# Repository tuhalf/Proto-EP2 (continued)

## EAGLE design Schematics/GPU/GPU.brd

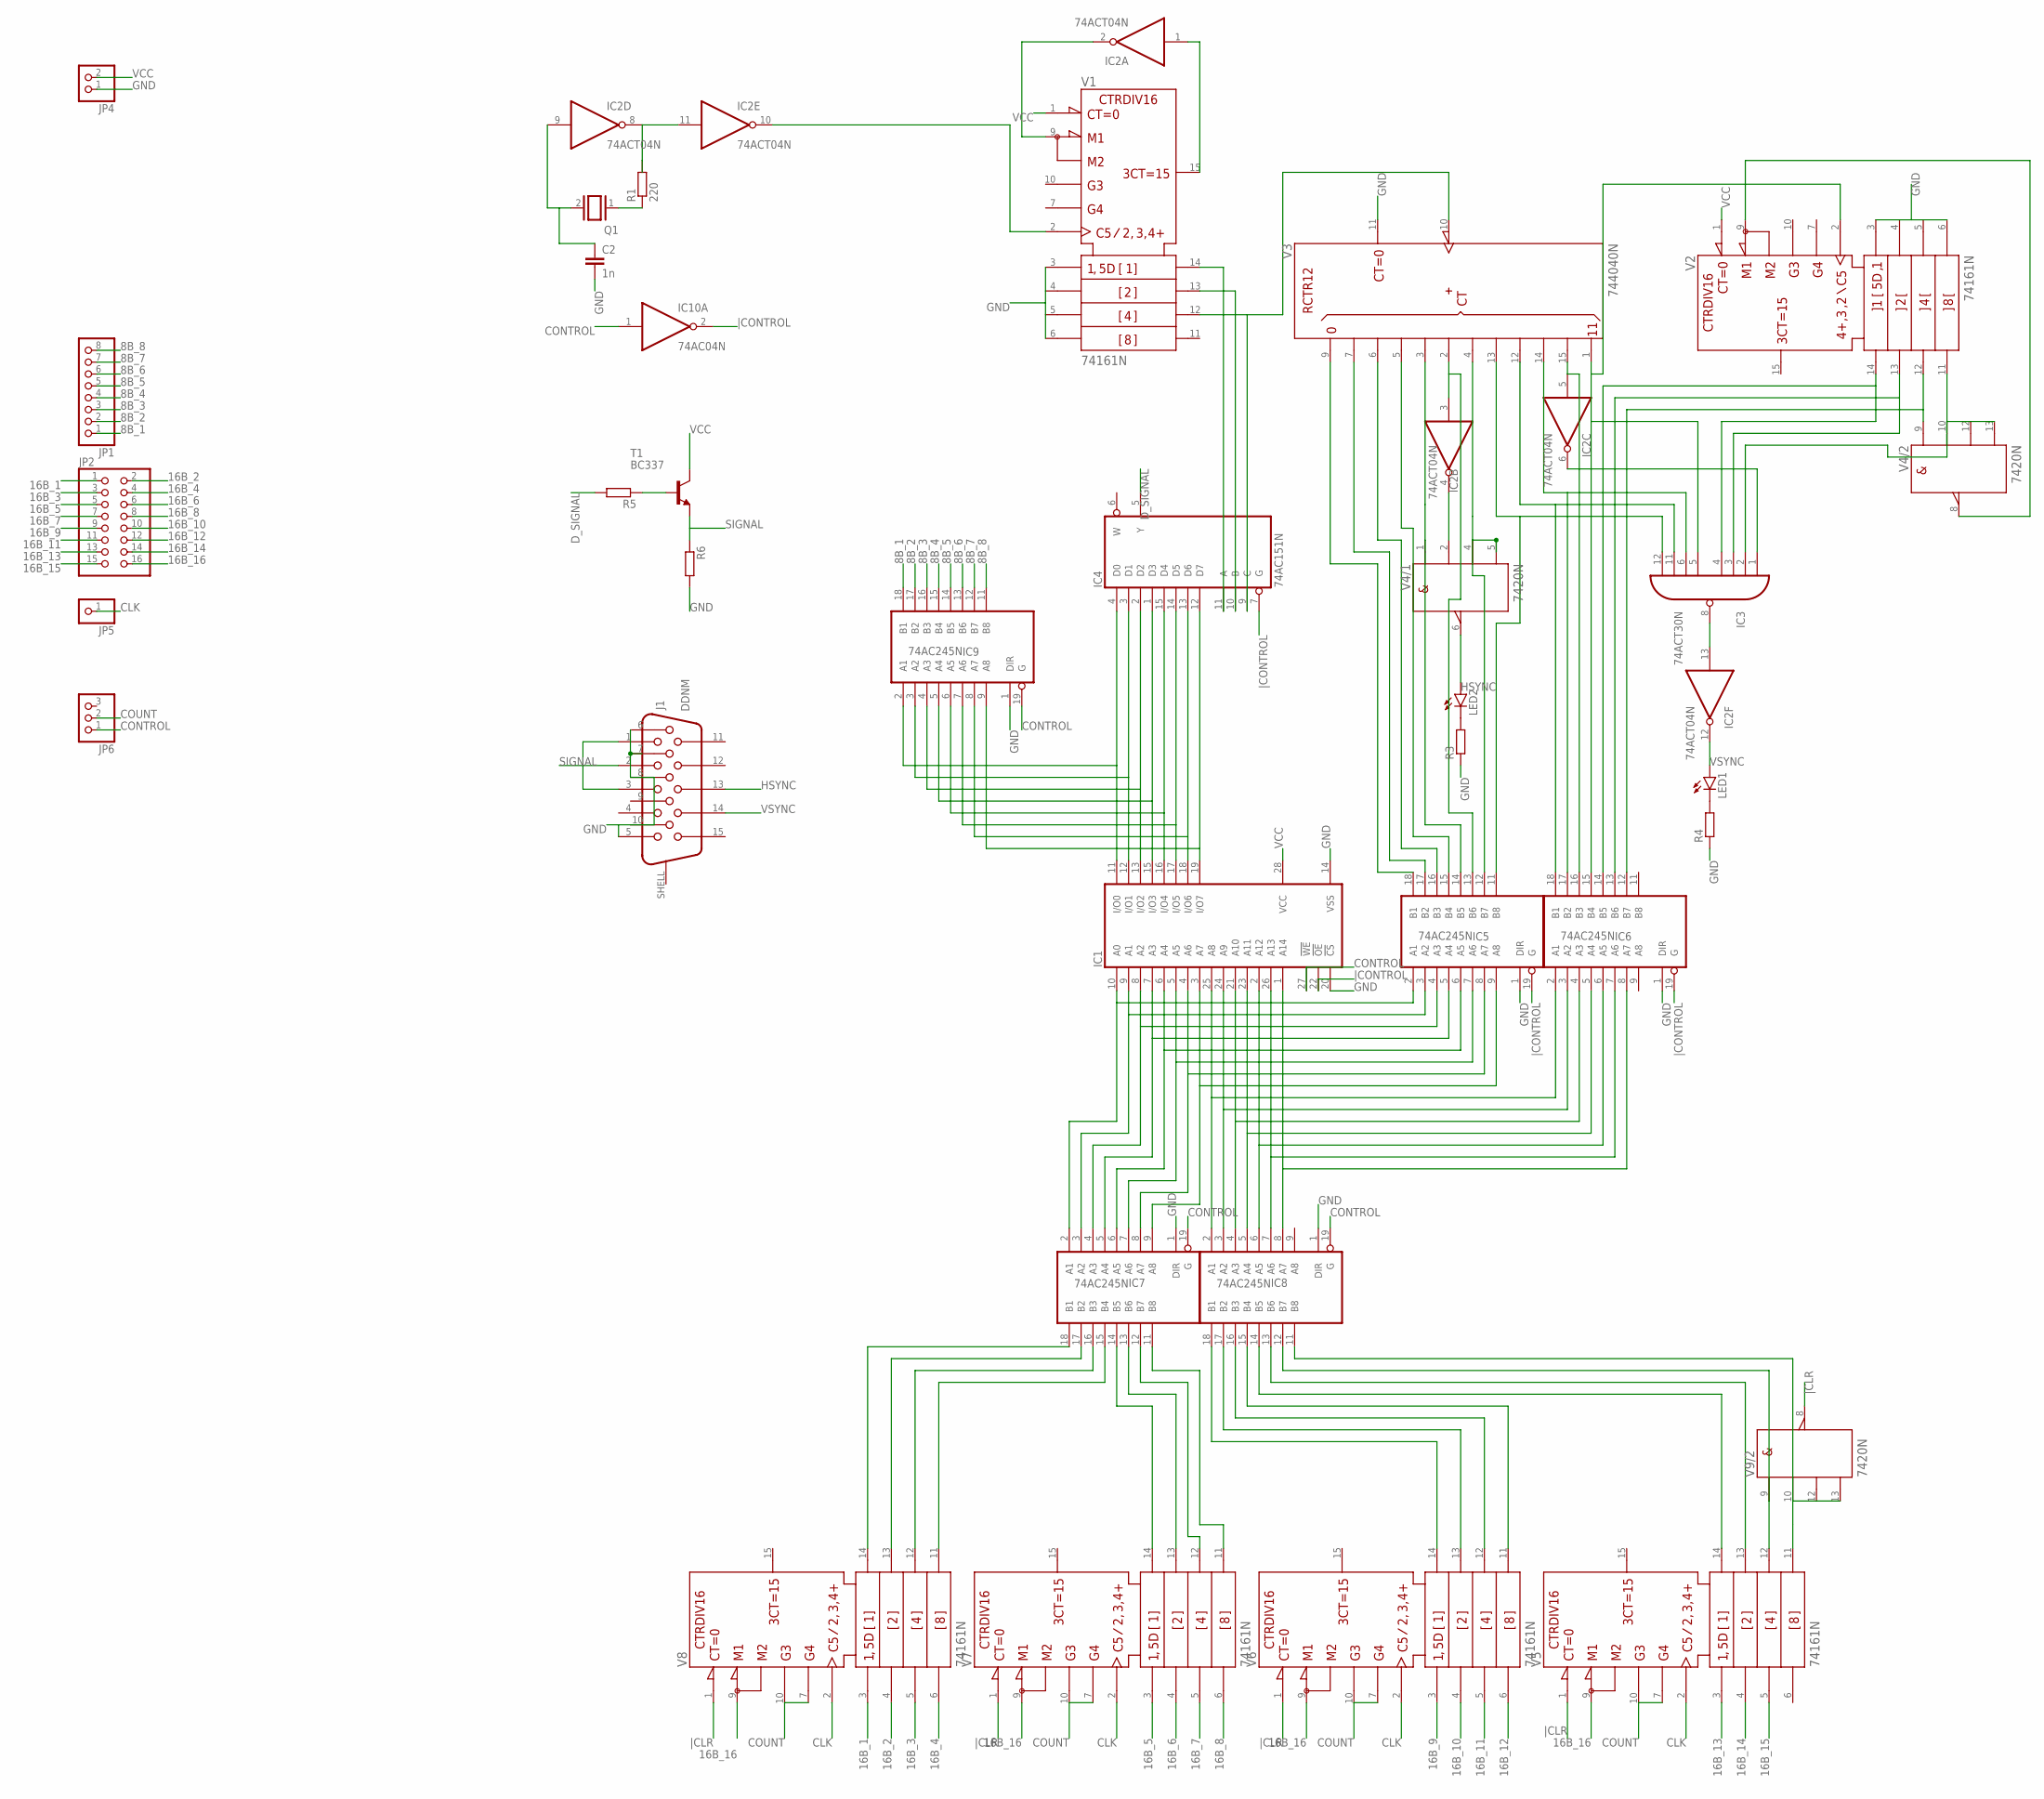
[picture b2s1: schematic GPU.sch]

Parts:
C2: 1n; C025-025X050
IC1: 62256P; DIL28-6
IC2: 74ACT04N; DIL14
IC3: 74ACT30N; DIL14
IC4: 74AC151N; DIL16
IC5, IC6, IC7, IC8, IC9: 74AC245N; DIL20
IC10: 74AC04N; DIL14
J1: DDNM; DNM
JP1: PINHD-1X8; 1X08
JP2: PINHD-2X8; 2X08
JP4: PINHD-1X2; 1X02
JP5: PINHD-1X1; 1X01
JP6: PINHD-1X3; 1X03
LED1, LED2: LED5MM
Q1: XTAL/S; QS
R1: 220; 0204/7
R3, R4, R5, R6: R-EU_0204/7; 0204/7
T1: BC337; TO92
V1, V2, V5, V6, V7, V8: 74161N; DIL16
V3: 744040N; DIL16
V4, V9: 7420N; DIL14

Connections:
8B_1: IC9.18 (B1), JP1.1
8B_2: IC9.17 (B2), JP1.2
8B_3: IC9.16 (B3), JP1.3
8B_4: IC9.15 (B4), JP1.4
8B_5: IC9.14 (B5), JP1.5
8B_6: IC9.13 (B6), JP1.6
8B_7: IC9.12 (B7), JP1.7
8B_8: IC9.11 (B8), JP1.8
16B_1: JP2.1, V8.3 (A)
16B_2: JP2.2, V8.4 (B)
16B_3: JP2.3, V8.5 (C)
16B_4: JP2.4, V8.6 (D)
16B_5: JP2.5, V7.3 (A)
16B_6: JP2.6, V7.4 (B)
16B_7: JP2.7, V7.5 (C)
16B_8: JP2.8, V7.6 (D)
16B_9: JP2.9, V6.3 (A)
16B_10: JP2.10, V6.4 (B)
16B_11: JP2.11, V6.5 (C)
16B_12: JP2.12, V6.6 (D)
16B_13: JP2.13, V5.3 (A)
16B_14: JP2.14, V5.4 (B)
16B_15: JP2.15, V5.5 (C)
16B_16: JP2.16, V5.9 (!LOAD), V6.9 (!LOAD), V7.9 (!LOAD), V8.9 (!LOAD)
+UB: V1.16 (+UB), V2.16 (+UB), V3.16 (+UB), V4.14 (+UB), V5.16 (+UB), V6.16 (+UB), V7.16 (+UB), V8.16 (+UB), V9.14 (+UB)
-UB: V1.8 (-UB), V2.8 (-UB), V3.8 (-UB), V4.7 (-UB), V5.8 (-UB), V6.8 (-UB), V7.8 (-UB), V8.8 (-UB), V9.7 (-UB)
CLK: JP5.1, V5.2 (CLK), V6.2 (CLK), V7.2 (CLK), V8.2 (CLK)
CONTROL: IC1.27 (!WE), IC7.19 (G), IC8.19 (G), IC9.19 (G), IC10.1 (I), JP6.1
COUNT: JP6.2, V5.7 (ENP), V5.10 (ENT), V6.7 (ENP), V6.10 (ENT), V7.7 (ENP), V7.10 (ENT), V8.7 (ENP), V8.10 (ENT)
D_SIGNAL: IC4.5 (Y), R5.2
GND: C2.2, IC1.14 (VSS), IC1.20 (!CS), IC2.7 (GND), IC3.7 (GND), IC4.8 (GND), IC5.1 (DIR), IC5.10 (GND), IC6.1 (DIR), IC6.10 (GND), IC7.1 (DIR), IC7.10 (GND), IC8.1 (DIR), IC8.10 (GND), IC9.1 (DIR), IC9.10 (GND), IC10.7 (GND), J1.5, J1.6, J1.7, J1.8, J1.10, JP4.1, R3.1, R4.1, R6.2, V1.3 (A), V1.4 (B), V1.5 (C), V1.6 (D), V2.3 (A), V2.4 (B), V2.5 (C), V2.6 (D), V3.11 (CLR)
HSYNC: J1.13, LED2.A, V4.6 (Y)
unnamed: C2.1, IC2.9 (I), Q1.2
unnamed: Q1.1, R1.1
unnamed: IC2.10 (O), V1.2 (CLK)
unnamed: IC2.2 (O), V1.9 (!LOAD)
unnamed: IC4.9 (C), V1.12 (QC), V3.10 (CLK)
unnamed: IC2.1 (I), V1.15 (RCO)
unnamed: IC5.18 (B1), V3.9 (QA)
unnamed: IC5.17 (B2), V3.7 (QB)
unnamed: IC5.14 (B5), V3.3 (QE), V4.1 (A)
unnamed: IC5.12 (B7), V3.4 (QG), V4.4 (C), V4.5 (D)
unnamed: IC3.5 (I4), IC6.15 (B4), V2.2 (CLK), V3.1 (QL)
unnamed: IC3.12 (I7), IC5.11 (B8), V3.13 (QH)
unnamed: V2.9 (!LOAD), V4.8 (Y)
unnamed: IC1.10 (A0), IC5.2 (A1), IC7.2 (A1)
unnamed: IC3.2 (I1), V2.11 (QD), V4.10 (B), V4.12 (C), V4.13 (D)
unnamed: IC3.11 (I6), IC6.18 (B1), V3.12 (QI)
unnamed: IC3.6 (I5), IC6.17 (B2), V3.14 (QJ)
unnamed: IC3.4 (I3), IC6.14 (B5), V2.14 (QA)
unnamed: IC3.3 (I2), IC6.13 (B6), V2.13 (QB)
unnamed: IC2.5 (I), IC6.16 (B3), V3.15 (QK)
unnamed: IC2.6 (O), IC3.1 (I0)
unnamed: IC2.13 (I), IC3.8 (O)
unnamed: IC4.11 (A), V1.14 (QA)
unnamed: IC4.10 (B), V1.13 (QB)
unnamed: IC5.16 (B3), V3.6 (QC)
unnamed: R5.1, T1.2 (B)
unnamed: LED2.K (C), R3.2
unnamed: LED1.K (C), R4.2
unnamed: IC2.8 (O), IC2.11 (I), R1.2
unnamed: IC5.15 (B4), V3.5 (QD)
unnamed: IC1.9 (A1), IC5.3 (A2), IC7.3 (A2)
unnamed: IC1.8 (A2), IC5.4 (A3), IC7.4 (A3)
unnamed: IC1.7 (A3), IC5.5 (A4), IC7.5 (A4)
unnamed: IC2.4 (O), V4.2 (B)
unnamed: IC1.6 (A4), IC5.6 (A5), IC7.6 (A5)
unnamed: IC6.12 (B7), V2.12 (QC), V4.9 (A)
unnamed: IC1.5 (A5), IC5.7 (A6), IC7.7 (A6)
unnamed: IC1.4 (A6), IC5.8 (A7), IC7.8 (A7)
unnamed: IC2.3 (I), IC5.13 (B6), V3.2 (QF)
unnamed: IC1.3 (A7), IC5.9 (A8), IC7.9 (A8)
unnamed: IC1.25 (A8), IC6.2 (A1), IC8.2 (A1)
unnamed: IC1.24 (A9), IC6.3 (A2), IC8.3 (A2)
unnamed: IC1.21 (A10), IC6.4 (A3), IC8.4 (A3)
unnamed: IC1.23 (A11), IC6.5 (A4), IC8.5 (A4)
unnamed: IC1.2 (A12), IC6.6 (A5), IC8.6 (A5)
unnamed: IC1.26 (A13), IC6.7 (A6), IC8.7 (A6)
unnamed: IC1.1 (A14), IC6.8 (A7), IC8.8 (A7)
unnamed: IC8.12 (B7), V5.12 (QC), V9.9 (A)
unnamed: IC8.11 (B8), V5.11 (QD), V9.10 (B), V9.12 (C), V9.13 (D)
unnamed: IC7.18 (B1), V8.14 (QA)
unnamed: IC7.17 (B2), V8.13 (QB)
unnamed: IC7.16 (B3), V8.12 (QC)
unnamed: IC7.15 (B4), V8.11 (QD)
unnamed: IC7.14 (B5), V7.14 (QA)
unnamed: IC7.13 (B6), V7.13 (QB)
unnamed: IC7.12 (B7), V7.12 (QC)
unnamed: IC7.11 (B8), V7.11 (QD)
unnamed: IC8.18 (B1), V6.14 (QA)
unnamed: IC8.13 (B6), V5.13 (QB)
unnamed: IC8.14 (B5), V5.14 (QA)
unnamed: IC8.15 (B4), V6.11 (QD)
unnamed: IC8.16 (B3), V6.12 (QC)
unnamed: IC8.17 (B2), V6.13 (QB)
unnamed: IC1.19 (I/O7), IC4.12 (D7), IC9.9 (A8)
unnamed: IC1.17 (I/O5), IC4.14 (D5), IC9.7 (A6)
unnamed: IC1.18 (I/O6), IC4.13 (D6), IC9.8 (A7)
unnamed: IC1.16 (I/O4), IC4.15 (D4), IC9.6 (A5)
unnamed: IC1.15 (I/O3), IC4.1 (D3), IC9.5 (A4)
unnamed: IC1.13 (I/O2), IC4.2 (D2), IC9.4 (A3)
unnamed: IC1.12 (I/O1), IC4.3 (D1), IC9.3 (A2)
unnamed: IC1.11 (I/O0), IC4.4 (D0), IC9.2 (A1)
SIGNAL: J1.1, J1.2, J1.3, R6.1, T1.1 (E)
VCC: IC1.28 (VCC), IC2.14 (VCC), IC3.14 (VCC), IC4.16 (VCC), IC5.20 (VCC), IC6.20 (VCC), IC7.20 (VCC), IC8.20 (VCC), IC9.20 (VCC), IC10.14 (VCC), JP4.2, T1.3 (C), V1.1 (!CLR), V2.1 (!CLR)
VSYNC: IC2.12 (O), J1.14, LED1.A
|CLR: V5.1 (!CLR), V6.1 (!CLR), V7.1 (!CLR), V8.1 (!CLR), V9.8 (Y)
|CONTROL: IC1.22 (!OE), IC4.7 (G), IC5.19 (G), IC6.19 (G), IC10.2 (O)

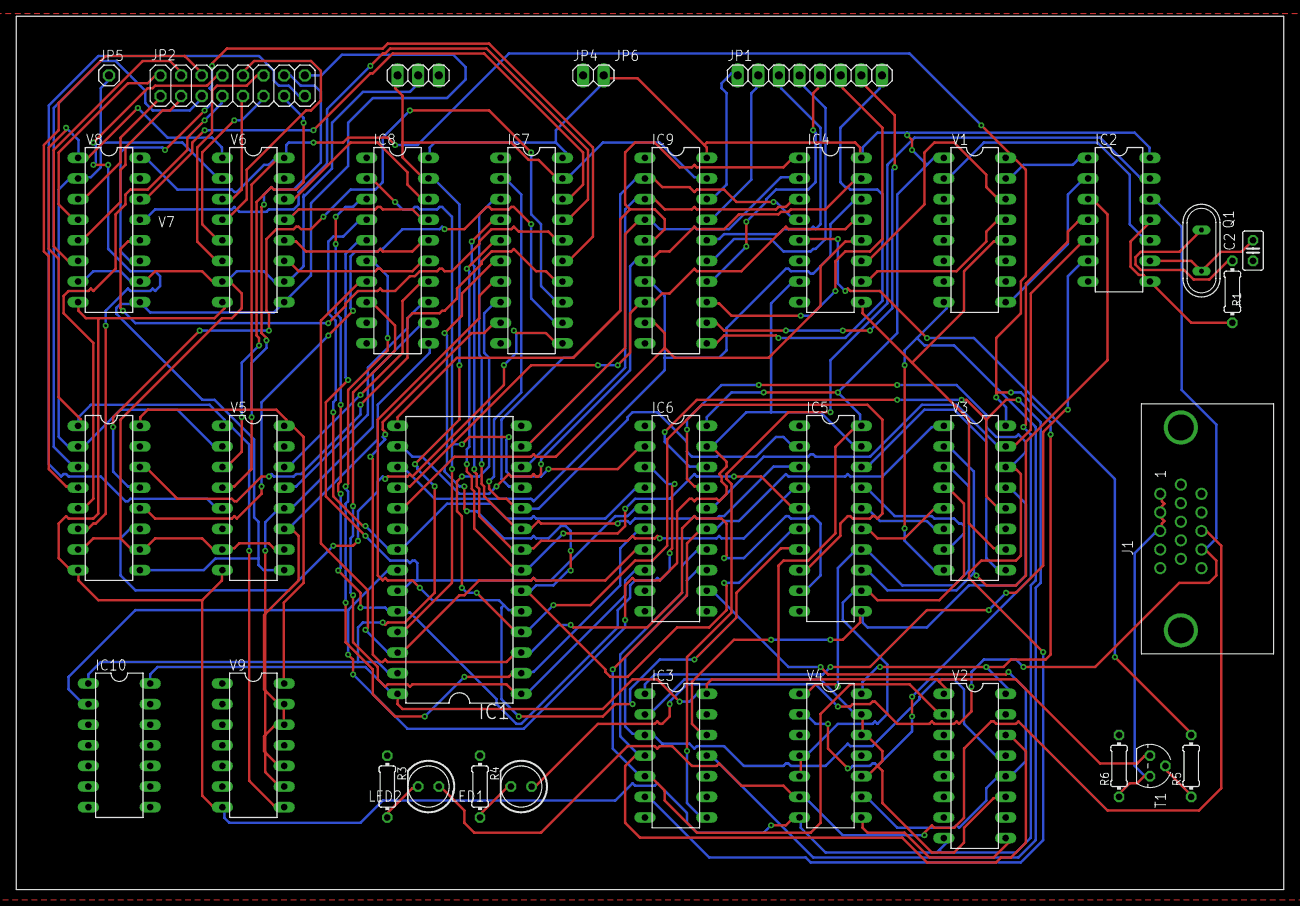
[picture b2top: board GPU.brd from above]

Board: 2 copper layers, 156.2 x 107.6 mm, 35 parts (0 on the bottom side), 108 nets.

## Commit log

2019-04-26 Simulation Created
2019-04-26 Perfected
2019-04-27 Bug Fix
2019-04-27 Started Eagle Drawings
2019-04-28 Some Modules Added
    Ram, Pc, A and B registers and ALU added.
2019-04-30 Schematics Are Done
2019-04-30 Some Changes
2019-05-01 made README better
2019-05-01 made README even better
2019-05-01 Added instruction set documentation
2019-05-03 All parts connected
2019-05-04 PCB Design Started
2019-05-04 Organized
2019-05-06 PCB Made Better
2019-05-09 Board Edited
2019-05-09 Small Fix
2019-05-10 Added renderings and autoroute schematics
2019-05-10 Added 3d design of front panel
2019-05-10 3D Design Updated
2019-05-10 Screenshots Moved
2019-05-16 Removed Unnecessary Files
2019-07-09 Boards Divided and Gpu Work Started
2019-07-11 Routd and Cams Created
2019-07-11 Design İmproved
2019-07-12 Visual Improvments
2019-08-19 Microcode Added and Ram Updated
2019-08-19 Gpu Updated
2019-09-14 added logo files
2019-09-14 added final logo files
2019-09-17 Bin Added and Sch Fixed
